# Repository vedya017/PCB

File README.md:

Arduino-Based Gas Sensor Detection System with Custom PCB Design

Designed and developed a custom PCB integrated with an Arduino Uno-based gas monitoring system for the detection of hazardous sewage gases, including hydrogen sulfide (H₂S), methane (CH₄), ammonia (NH₃), and carbon monoxide (CO). The system continuously acquires gas concentration data from multiple gas sensors, processes the readings through the Arduino controller, and compares them against predefined safety thresholds. When gas levels exceed permissible limits, the system generates immediate alerts through output indicators to warn workers of potentially dangerous conditions. Real-time gas concentration values are displayed on an LCD screen, LED lights, and buzzers for appropriate warning levels, enabling continuous environmental monitoring and improving safety in sewage and confined-space operations.

Project Flow:
Gas Sensors → Signal Acquisition → Arduino Uno Processing → Threshold Comparison → LCD Display of Gas Concentrations → Hazard Detection → Alert/Warning Generation for Workers.

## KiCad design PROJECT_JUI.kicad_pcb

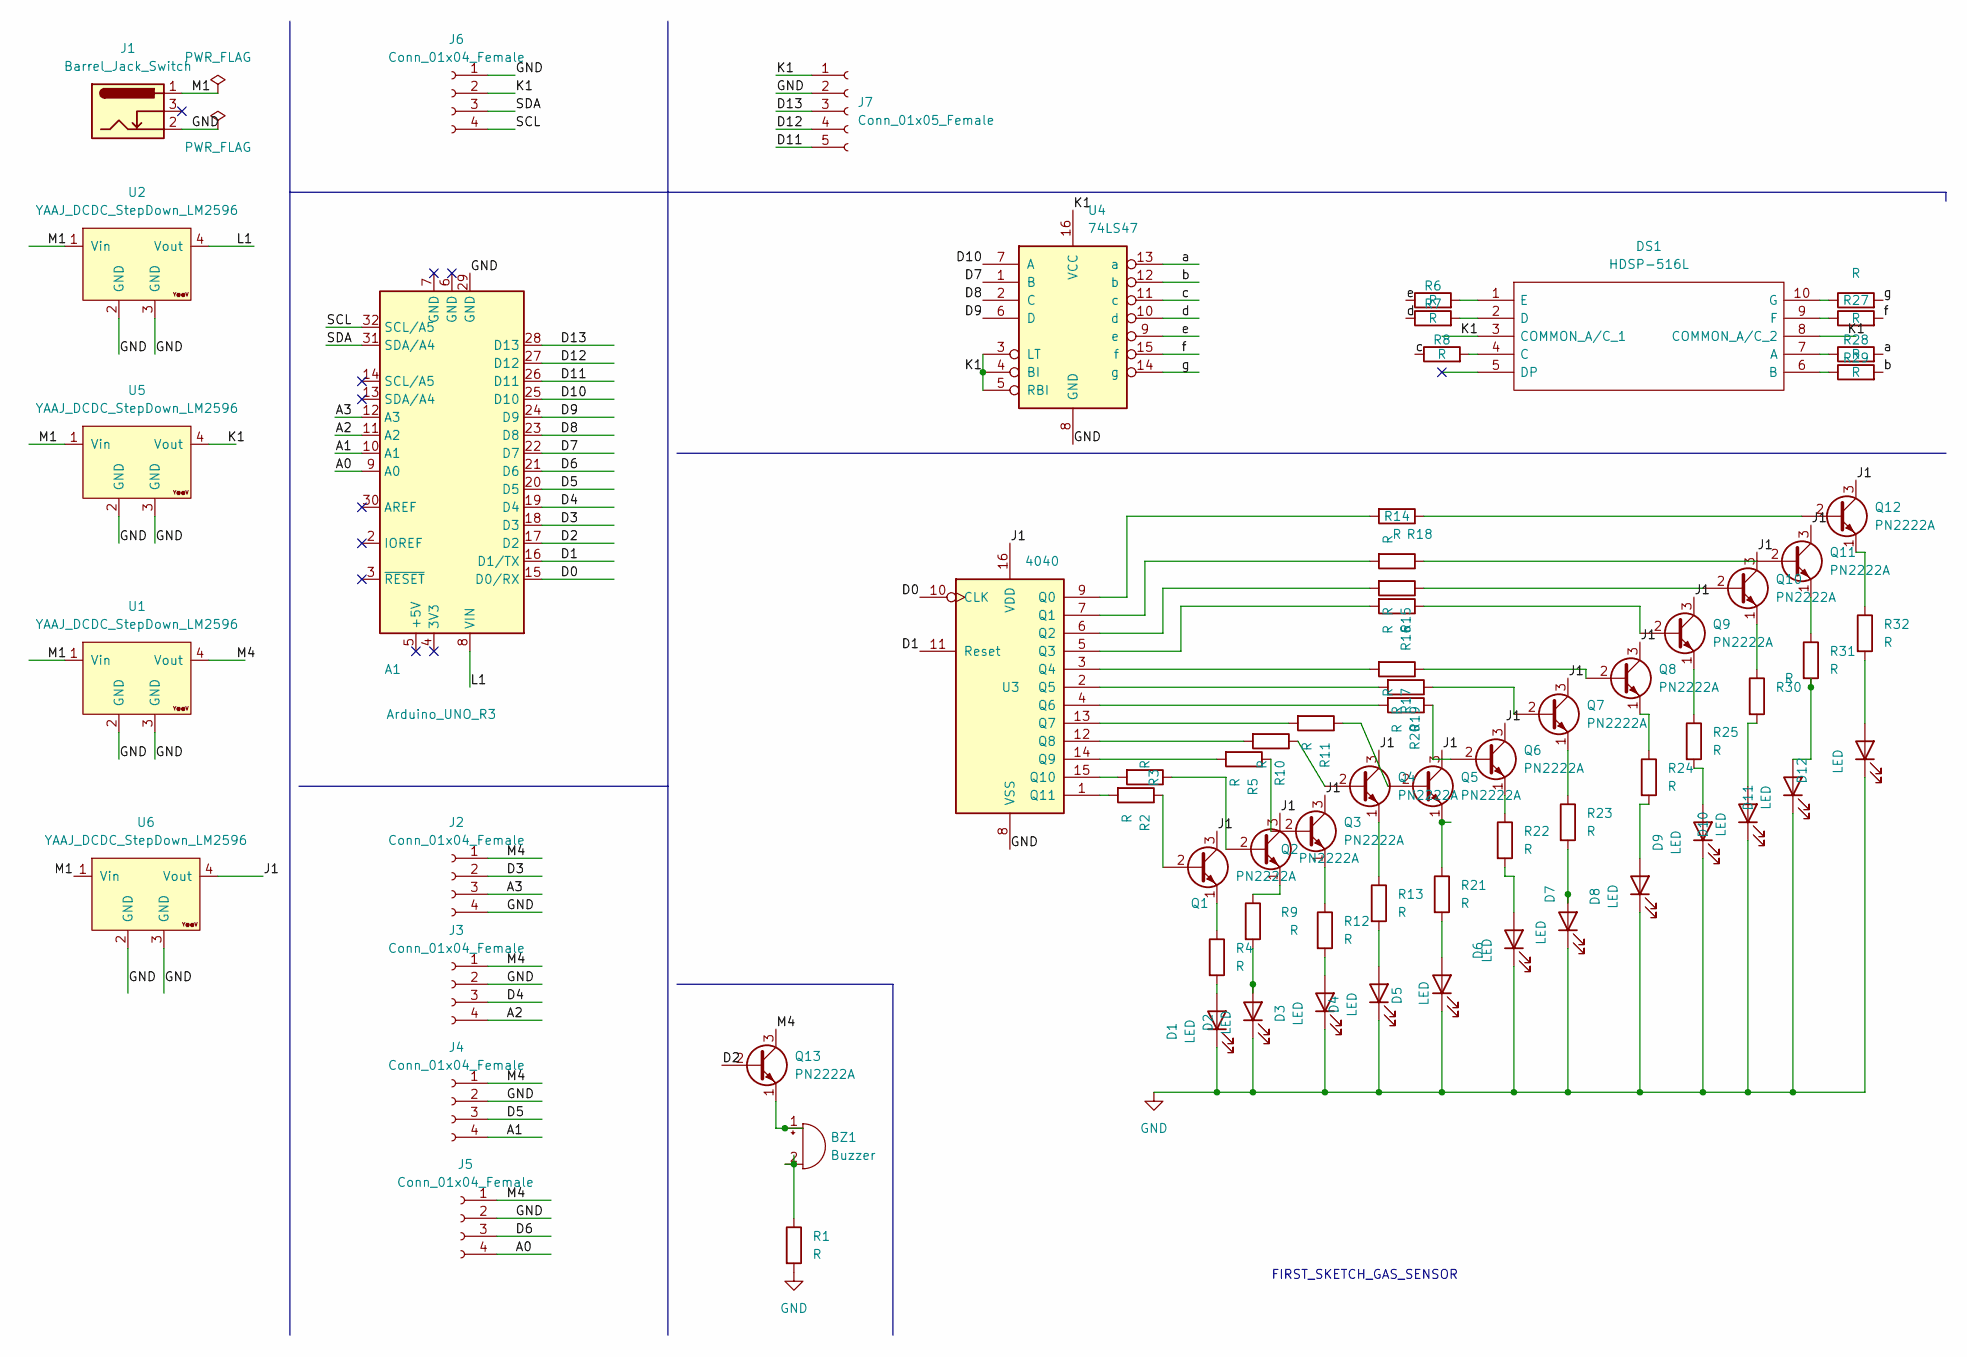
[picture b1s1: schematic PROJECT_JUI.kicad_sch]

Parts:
A1: Arduino_UNO_R3; Arduino_UNO_R3_WithMountingHoles
BZ1: Buzzer; Buzzer_12x9.5RM7.6
D1, D2, D3, D4, D5, D6, D7, D8, D9, D10, D11, D12: LED; LED_0201_0603Metric
DS1: HDSP-516L; LED_HDSP-511Y; Manufacturer_Part_Number HDSP-516L; Mouser Part Number 630-HDSP-516L
J1: Barrel_Jack_Switch; BarrelJack_Wuerth_6941xx301002
J2, J3, J4, J5, J6: Conn_01x04_Female; PinHeader_1x04_P2.54mm_Vertical
J7: Conn_01x05_Female; PinHeader_1x05_P2.54mm_Vertical
Q1, Q2, Q3, Q4, Q5, Q6, Q7, Q8, Q9, Q10, Q11, Q12, Q13: PN2222A; TO-92L_Inline_Wide
R1, R2, R3, R4, R5, R6, R7, R8, R9, R10, R11, R12, R13, R14, R15, R16, R17, R18, R19, R20, R21, R22, R23, R24, R25, R26, R27, R28, R29, R30, R31, R32: R; R_Axial_DIN0309_L9.0mm_D3.2mm_P12.70mm_Horizontal
U1, U2, U5, U6: YAAJ_DCDC_StepDown_LM2596
U3: 4040; DIP-16_W7.62mm_Socket
U4: 74LS47; DIP-16_W7.62mm_Socket

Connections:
/A0: A1.9 (A0), J5.4
/A1: A1.10 (A1), J4.4
/A2: A1.11 (A2), J3.4
/A3: A1.12 (A3), J2.3
/D0: A1.15 (D0/RX), U3.10 (CLK)
/D1: A1.16 (D1/TX), U3.11 (Reset)
/D2: A1.17 (D2), Q13.2 (B)
/D3: A1.18 (D3), J2.2
/D4: A1.19 (D4), J3.3
/D5: A1.20 (D5), J4.3
/D6: A1.21 (D6), J5.3
/D7: A1.22 (D7), U4.1 (B)
/D8: A1.23 (D8), U4.2 (C)
/D9: A1.24 (D9), U4.6 (D)
/D10: A1.25 (D10), U4.7 (A)
/D11: A1.26 (D11), J7.5
/D12: A1.27 (D12), J7.4
/D13: A1.28 (D13), J7.3
/J1: Q1.3 (C), Q2.3 (C), Q3.3 (C), Q4.3 (C), Q5.3 (C), Q6.3 (C), Q7.3 (C), Q8.3 (C), Q9.3 (C), Q10.3 (C), Q11.3 (C), Q12.3 (C), U3.16 (VDD), U6.4 (Vout)
/K1: DS1.3 (COMMON_A/C_1), DS1.8 (COMMON_A/C_2), J6.2, J7.1, U4.3 (LT), U4.4 (BI), U4.5 (RBI), U4.16 (VCC), U5.4 (Vout)
/L1: A1.8 (VIN), U2.4 (Vout)
/M1: J1.1, U1.1 (Vin), U2.1 (Vin), U5.1 (Vin), U6.1 (Vin)
/M4: J2.1, J3.1, J4.1, J5.1, Q13.3 (C), U1.4 (Vout)
/SCL: A1.32 (SCL/A5), J6.4
/SDA: A1.31 (SDA/A4), J6.3
/a: R28.2, U4.13 (a)
/b: R29.2, U4.12 (b)
/c: R8.1, U4.11 (c)
/d: R7.1, U4.10 (d)
/e: R6.1, U4.9 (e)
/f: R27.2, U4.15 (f)
/g: R26.2, U4.14 (g)
GND: A1.29 (GND), D1.1 (K), D2.1 (K), D3.1 (K), D4.1 (K), D5.1 (K), D6.1 (K), D7.1 (K), D8.1 (K), D9.1 (K), D10.1 (K), D11.1 (K), D12.1 (K), J1.2, J2.4, J3.2, J4.2, J5.2, J6.1, J7.2, R1.2, U1.2 (GND), U1.3 (GND), U2.2 (GND), U2.3 (GND), U3.8 (VSS), U4.8 (GND), U5.2 (GND), U5.3 (GND), U6.2 (GND), U6.3 (GND)
unnamed: BZ1.1 (-), Q13.1 (E)
unnamed: BZ1.2 (+), R1.1
unnamed: D1.2 (A), R4.2
unnamed: D2.2 (A), R9.2
unnamed: D3.2 (A), R12.2
unnamed: D4.2 (A), R13.2
unnamed: D5.2 (A), R21.2
unnamed: D6.2 (A), R22.2
unnamed: D7.2 (A), R23.2
unnamed: D8.2 (A), R24.2
unnamed: D9.2 (A), R25.2
unnamed: D10.2 (A), R30.2
unnamed: D11.2 (A), R31.2
unnamed: D12.2 (A), R32.2
unnamed: DS1.1 (E), R6.2
unnamed: DS1.2 (D), R7.2
unnamed: DS1.4 (C), R8.2
unnamed: DS1.6 (B), R29.1
unnamed: DS1.7 (A), R28.1
unnamed: DS1.9 (F), R27.1
unnamed: DS1.10 (G), R26.1
unnamed: Q1.1 (E), R4.1
unnamed: Q1.2 (B), R2.1
unnamed: Q2.1 (E), R9.1
unnamed: Q2.2 (B), R3.1
unnamed: Q3.1 (E), R12.1
unnamed: Q3.2 (B), R5.1
unnamed: Q4.1 (E), R13.1
unnamed: Q4.2 (B), R10.1
unnamed: Q5.1 (E), R21.1
unnamed: Q5.2 (B), R11.1
unnamed: Q6.1 (E), R22.1
unnamed: Q6.2 (B), R20.1
unnamed: Q7.1 (E), R23.1
unnamed: Q7.2 (B), R19.1
unnamed: Q8.1 (E), R24.1
unnamed: Q8.2 (B), R17.1
unnamed: Q9.1 (E), R25.1
unnamed: Q9.2 (B), R16.1
unnamed: Q10.1 (E), R30.1
unnamed: Q10.2 (B), R15.1
unnamed: Q11.1 (E), R31.1
unnamed: Q11.2 (B), R14.1
unnamed: Q12.1 (E), R32.1
unnamed: Q12.2 (B), R18.1
unnamed: R2.2, U3.1 (Q11)
unnamed: R3.2, U3.15 (Q10)
unnamed: R5.2, U3.14 (Q9)
unnamed: R10.2, U3.12 (Q8)
unnamed: R11.2, U3.13 (Q7)
unnamed: R14.2, U3.7 (Q1)
unnamed: R15.2, U3.6 (Q2)
unnamed: R16.2, U3.5 (Q3)
unnamed: R17.2, U3.3 (Q4)
unnamed: R18.2, U3.9 (Q0)
unnamed: R19.2, U3.2 (Q5)
unnamed: R20.2, U3.4 (Q6)

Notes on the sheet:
FIRST_SKETCH_GAS_SENSOR

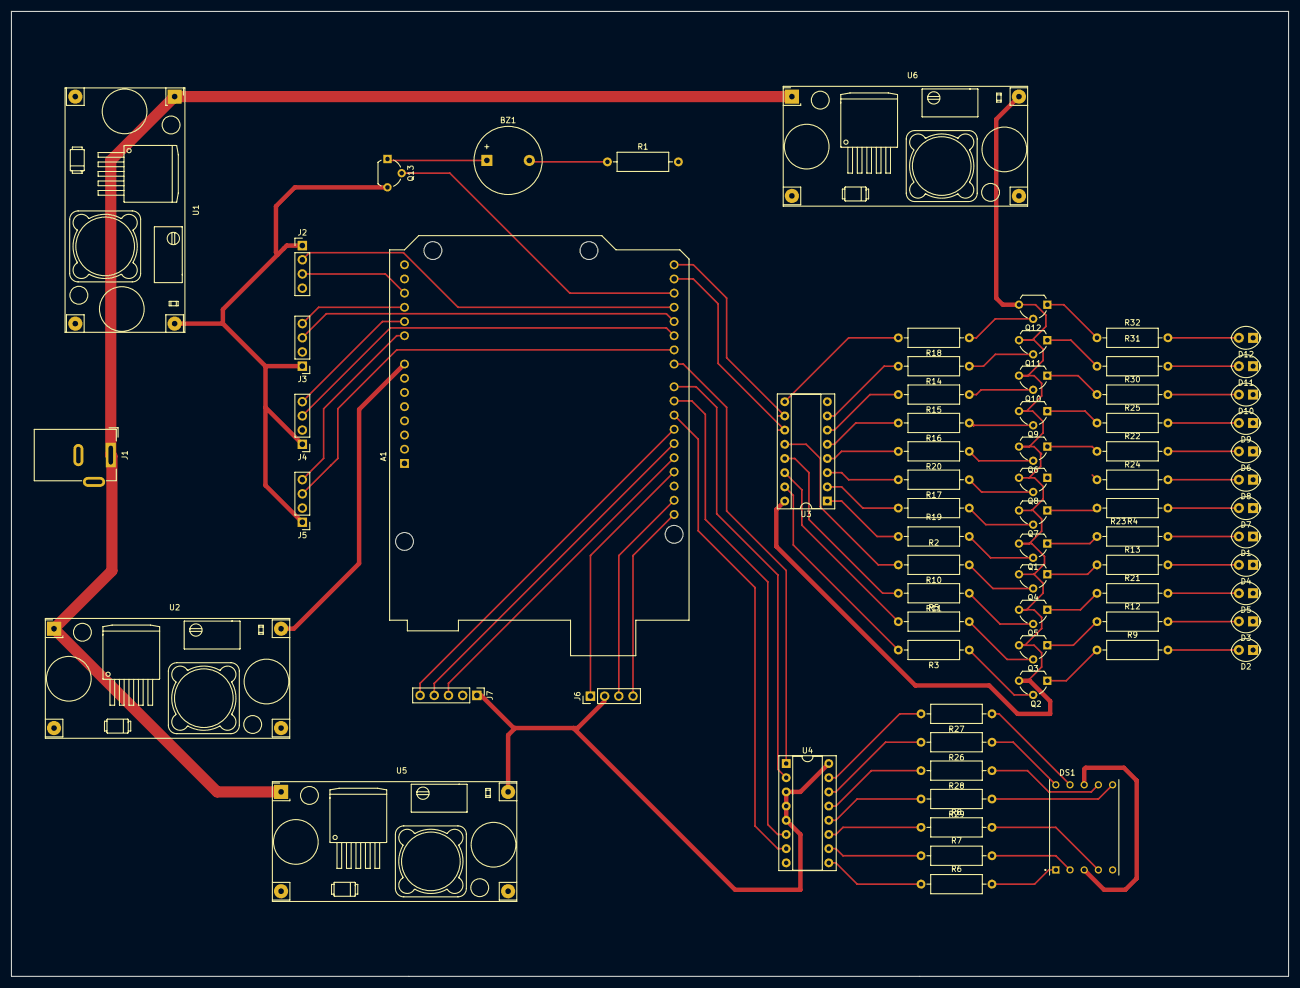
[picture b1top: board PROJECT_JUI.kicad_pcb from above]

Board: 2 copper layers, 228.6 x 172.7 mm, 73 parts (0 on the bottom side), 90 nets.

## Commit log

2025-09-11 KiCAD schematic and pcb files
2025-09-11 SRF Project Report
2026-06-03 Integrated Code for all components
2026-06-03 Code for MQ137 gas sensor
